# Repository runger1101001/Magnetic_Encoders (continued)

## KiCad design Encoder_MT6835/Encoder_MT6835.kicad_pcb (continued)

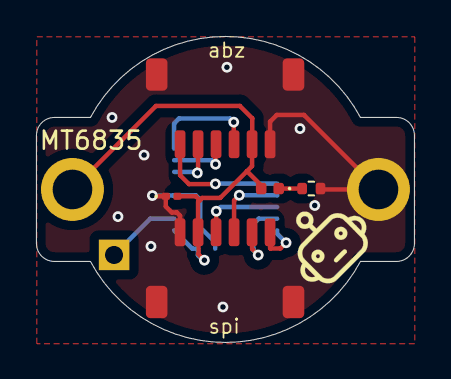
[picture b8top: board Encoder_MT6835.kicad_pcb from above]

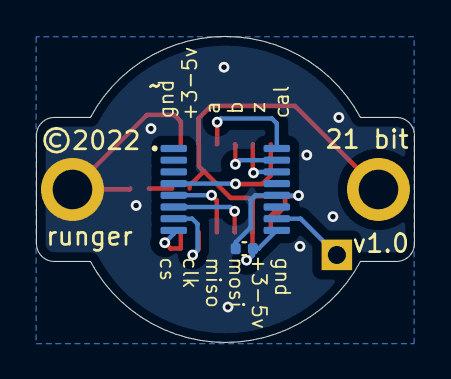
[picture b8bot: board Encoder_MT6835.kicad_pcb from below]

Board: 2 copper layers, 21.0 x 17.0 mm, 11 parts (2 on the bottom side), 12 nets.

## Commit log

2021-10-22 first import of all the encoder projects
2022-01-18 Encoder_SPI update for new assembly order
2022-01-18 added readme and documentation images
2022-01-18 README update
2022-01-23 add PCB images and update README
2022-01-27 A1334 encoder design first production run
2022-01-27 added license updated README
2022-01-27 updated docs for AS5048A sensor
2022-02-08 Added design based on SC60228 encoder
2022-02-17 Update README.md
    Added link to SmallRobots discord server
2022-05-04 new encoder models, updated READMEs
2022-11-05 Created a MT6835 encoder board with SPI and ABZ
2022-11-08 fix incorrect footprint
2022-11-08 update labels
2022-11-08 added sc60228 pics
2022-11-08 add 3d models, fix bugs
2022-11-08 update READMEs
2022-11-09 production v1
2023-05-14 Encoder updates
2023-09-22 update datasheet URL
2023-09-22 Add AS5047P encoder board
2023-10-20 added AS5600 encoder (unfinished)
2024-01-18 Working on docs for AS5047P
2024-01-19 Update SC60228 docs
2024-09-27 MT6835 docs update
2024-09-27 project file changes
2024-09-27 AS5600 I2C encoder board and panel
2024-09-27 AS5047P encoder changes
2025-10-08 new encoders - KTH7812, MT6816, MT6826S
2026-01-04 encoder small changes
